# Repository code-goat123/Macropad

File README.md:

# Aryav's Macropad

MiPad is a 3x3 macropad that is made for KMK firmware.

## Features:
- Sleek squircle design
- 9 Kailh low-profile switches
- Two-tone

## CAD Model:
Everything fits in together by slotting into the parts. I plan to improve the mounting mechanism in the future (and will likely have to fine tune some things once I have the PCB), but for now it just uses slot mechanisms. 

There are 2 parts to the case: the top face and the bottom casing. I made it in Fusion360.  

## PCB
I made the PCB in KiCad, and used KiBuzzard to make the fun text. 

Schematic

PCB

I used Kailh's choc v2 key switch footprints, but used MX style spacing in this build. 

## Firmware Overview
This hackpad uses KMK firmware for everything. 

- the 6 keys are currently used for media controls for music, screen brightness changers, and a layer switch. 
- currently, I only have 1 layer implemented, but I'm going to be adding some more later on. 
- the OLED currently displays layer # and I plan to add some woodstock animations in the future.

## BOM:

- 9x Kailh Spring Mini Low-Profile Switches (I have these already, from another build)
- 9x Choc-v2 compatible Keycaps (I also have these already from another build)
- 1x PCB
- 1x XIAO RP2040
- 1x Case (2 printed parts)

## Final Picture:

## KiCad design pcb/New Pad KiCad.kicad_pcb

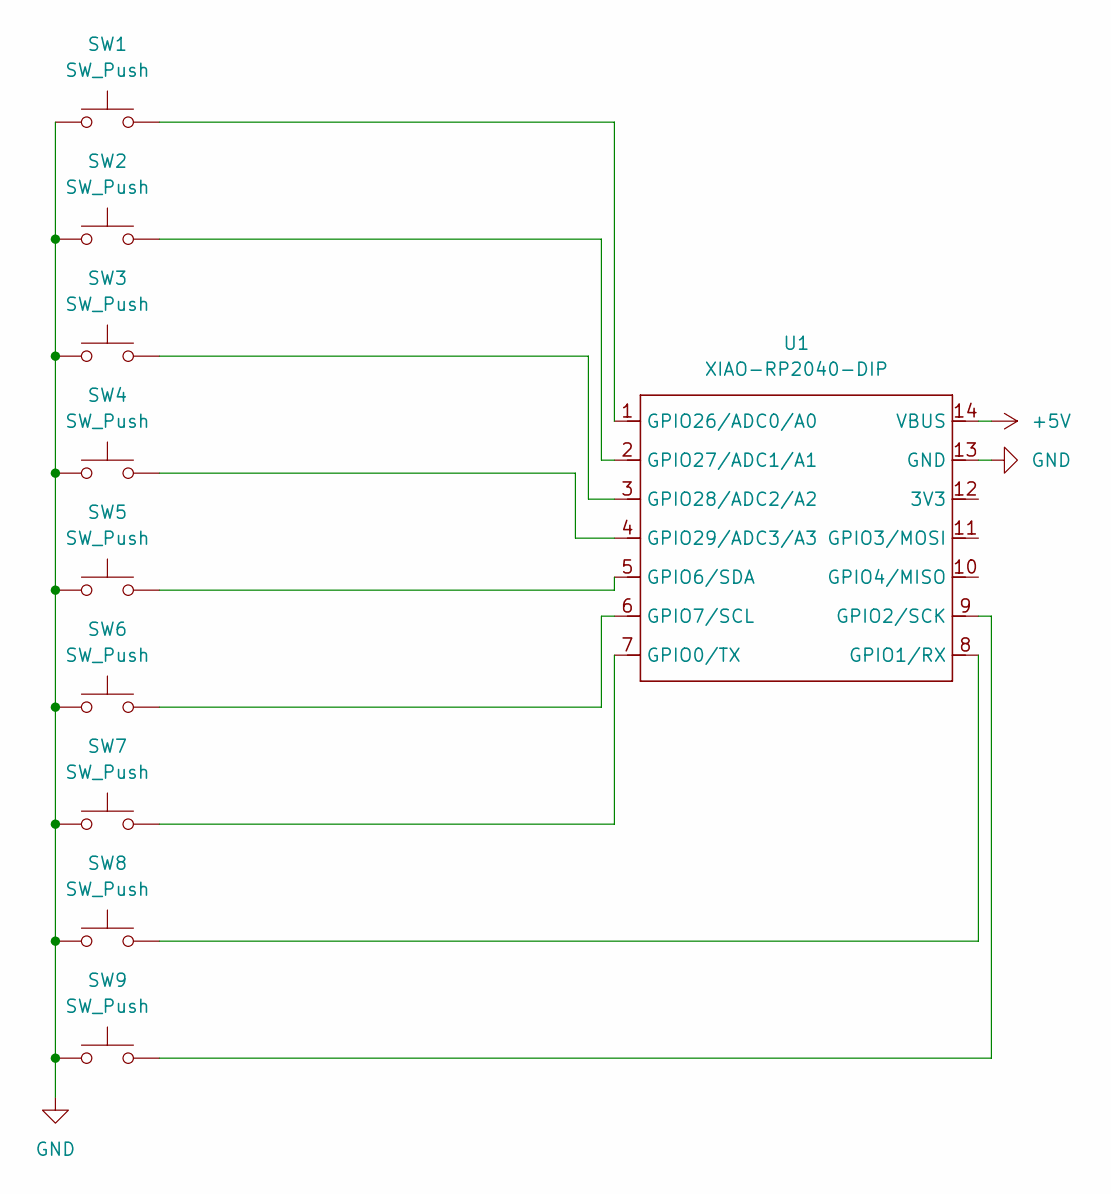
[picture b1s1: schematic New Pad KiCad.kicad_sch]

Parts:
SW1, SW2, SW3, SW4, SW5, SW6, SW7, SW8, SW9: SW_Push; Kailh-PG1353-Solderable-1U
U1: XIAO-RP2040-DIP

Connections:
+5V: U1.14 (VBUS)
GND: SW1.1, SW2.1, SW3.1, SW4.1, SW5.1, SW6.1, SW7.1, SW8.1, SW9.1, U1.13 (GND)
unnamed: SW7.2, U1.7 (GPIO0/TX)
unnamed: SW8.2, U1.8 (GPIO1/RX)
unnamed: SW9.2, U1.9 (GPIO2/SCK)
unnamed: SW5.2, U1.5 (GPIO6/SDA)
unnamed: SW6.2, U1.6 (GPIO7/SCL)
unnamed: SW1.2, U1.1 (GPIO26/ADC0/A0)
unnamed: SW2.2, U1.2 (GPIO27/ADC1/A1)
unnamed: SW3.2, U1.3 (GPIO28/ADC2/A2)
unnamed: SW4.2, U1.4 (GPIO29/ADC3/A3)

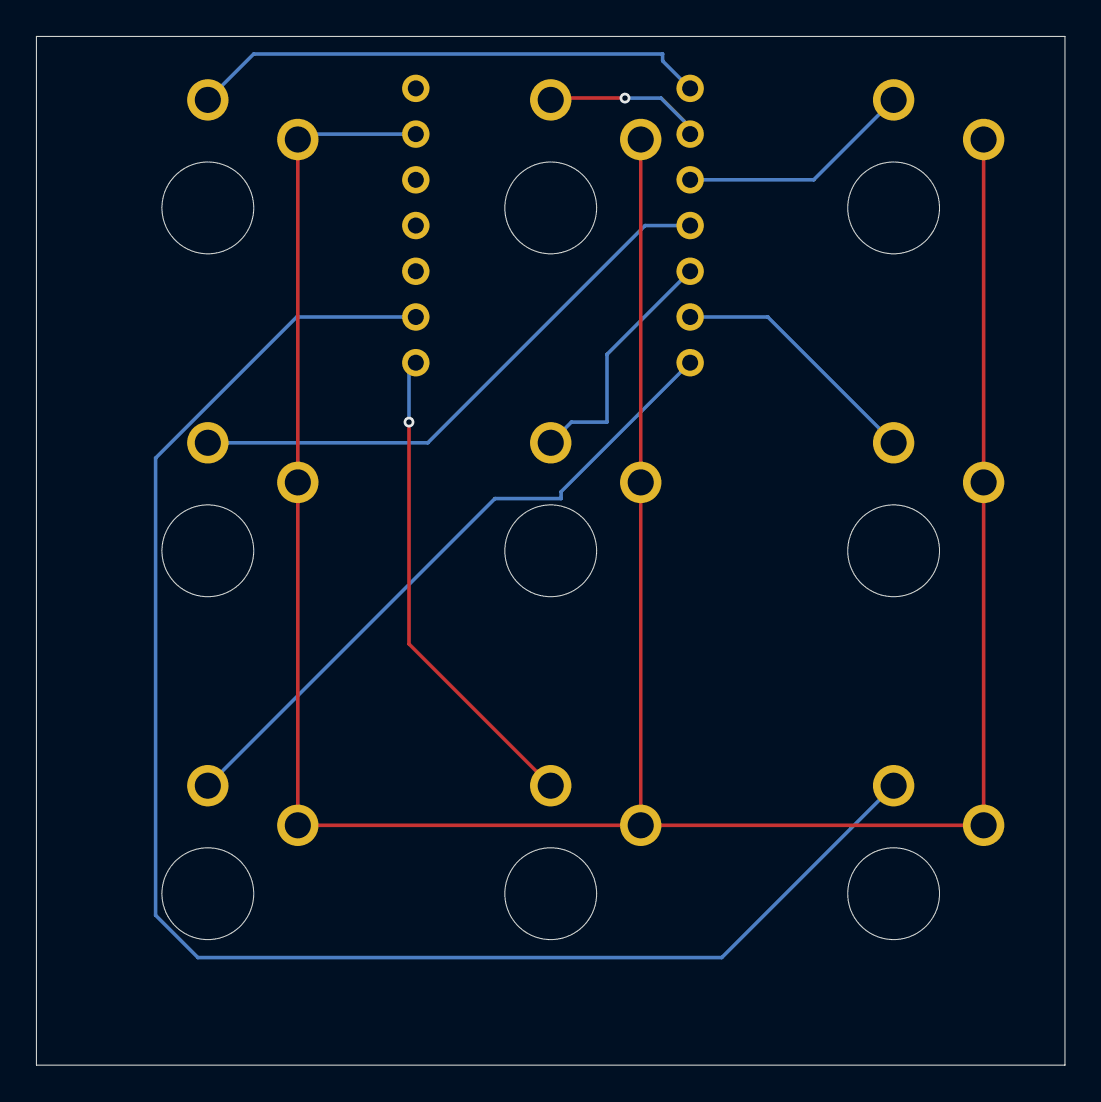
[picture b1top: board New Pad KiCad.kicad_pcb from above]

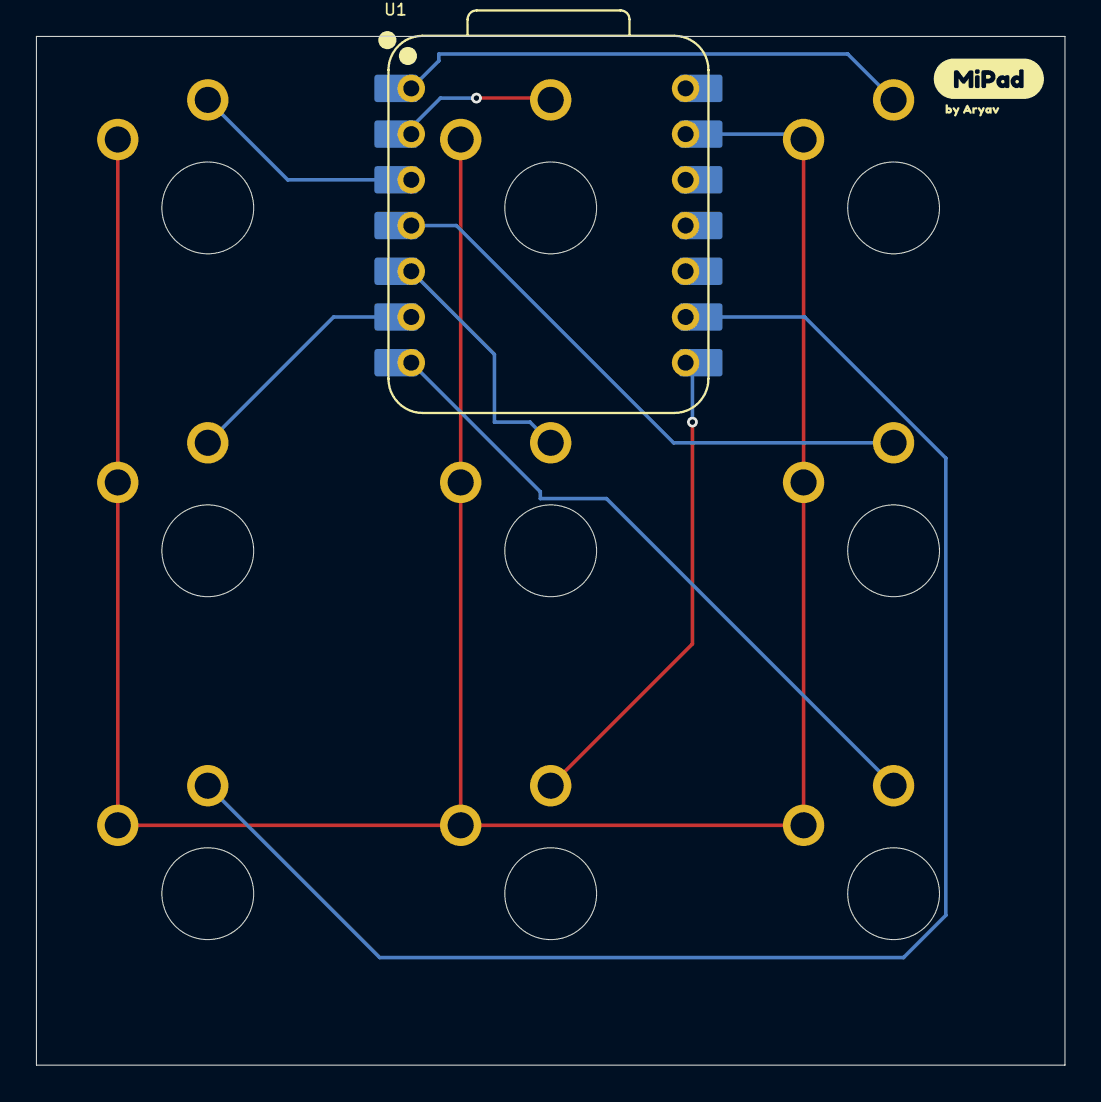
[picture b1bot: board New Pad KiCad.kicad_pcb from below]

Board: 2 copper layers, 57.1 x 57.2 mm, 12 parts (3 on the bottom side), 10 nets.

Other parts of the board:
kibuzzard-692BA7AE: G***; kibuzzard-692BA7AE
kibuzzard-692BA7D5: G***; kibuzzard-692BA7D5

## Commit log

2026-04-21 Initial commit
    Add project files and README with final build photo.
    Made-with: Cursor
